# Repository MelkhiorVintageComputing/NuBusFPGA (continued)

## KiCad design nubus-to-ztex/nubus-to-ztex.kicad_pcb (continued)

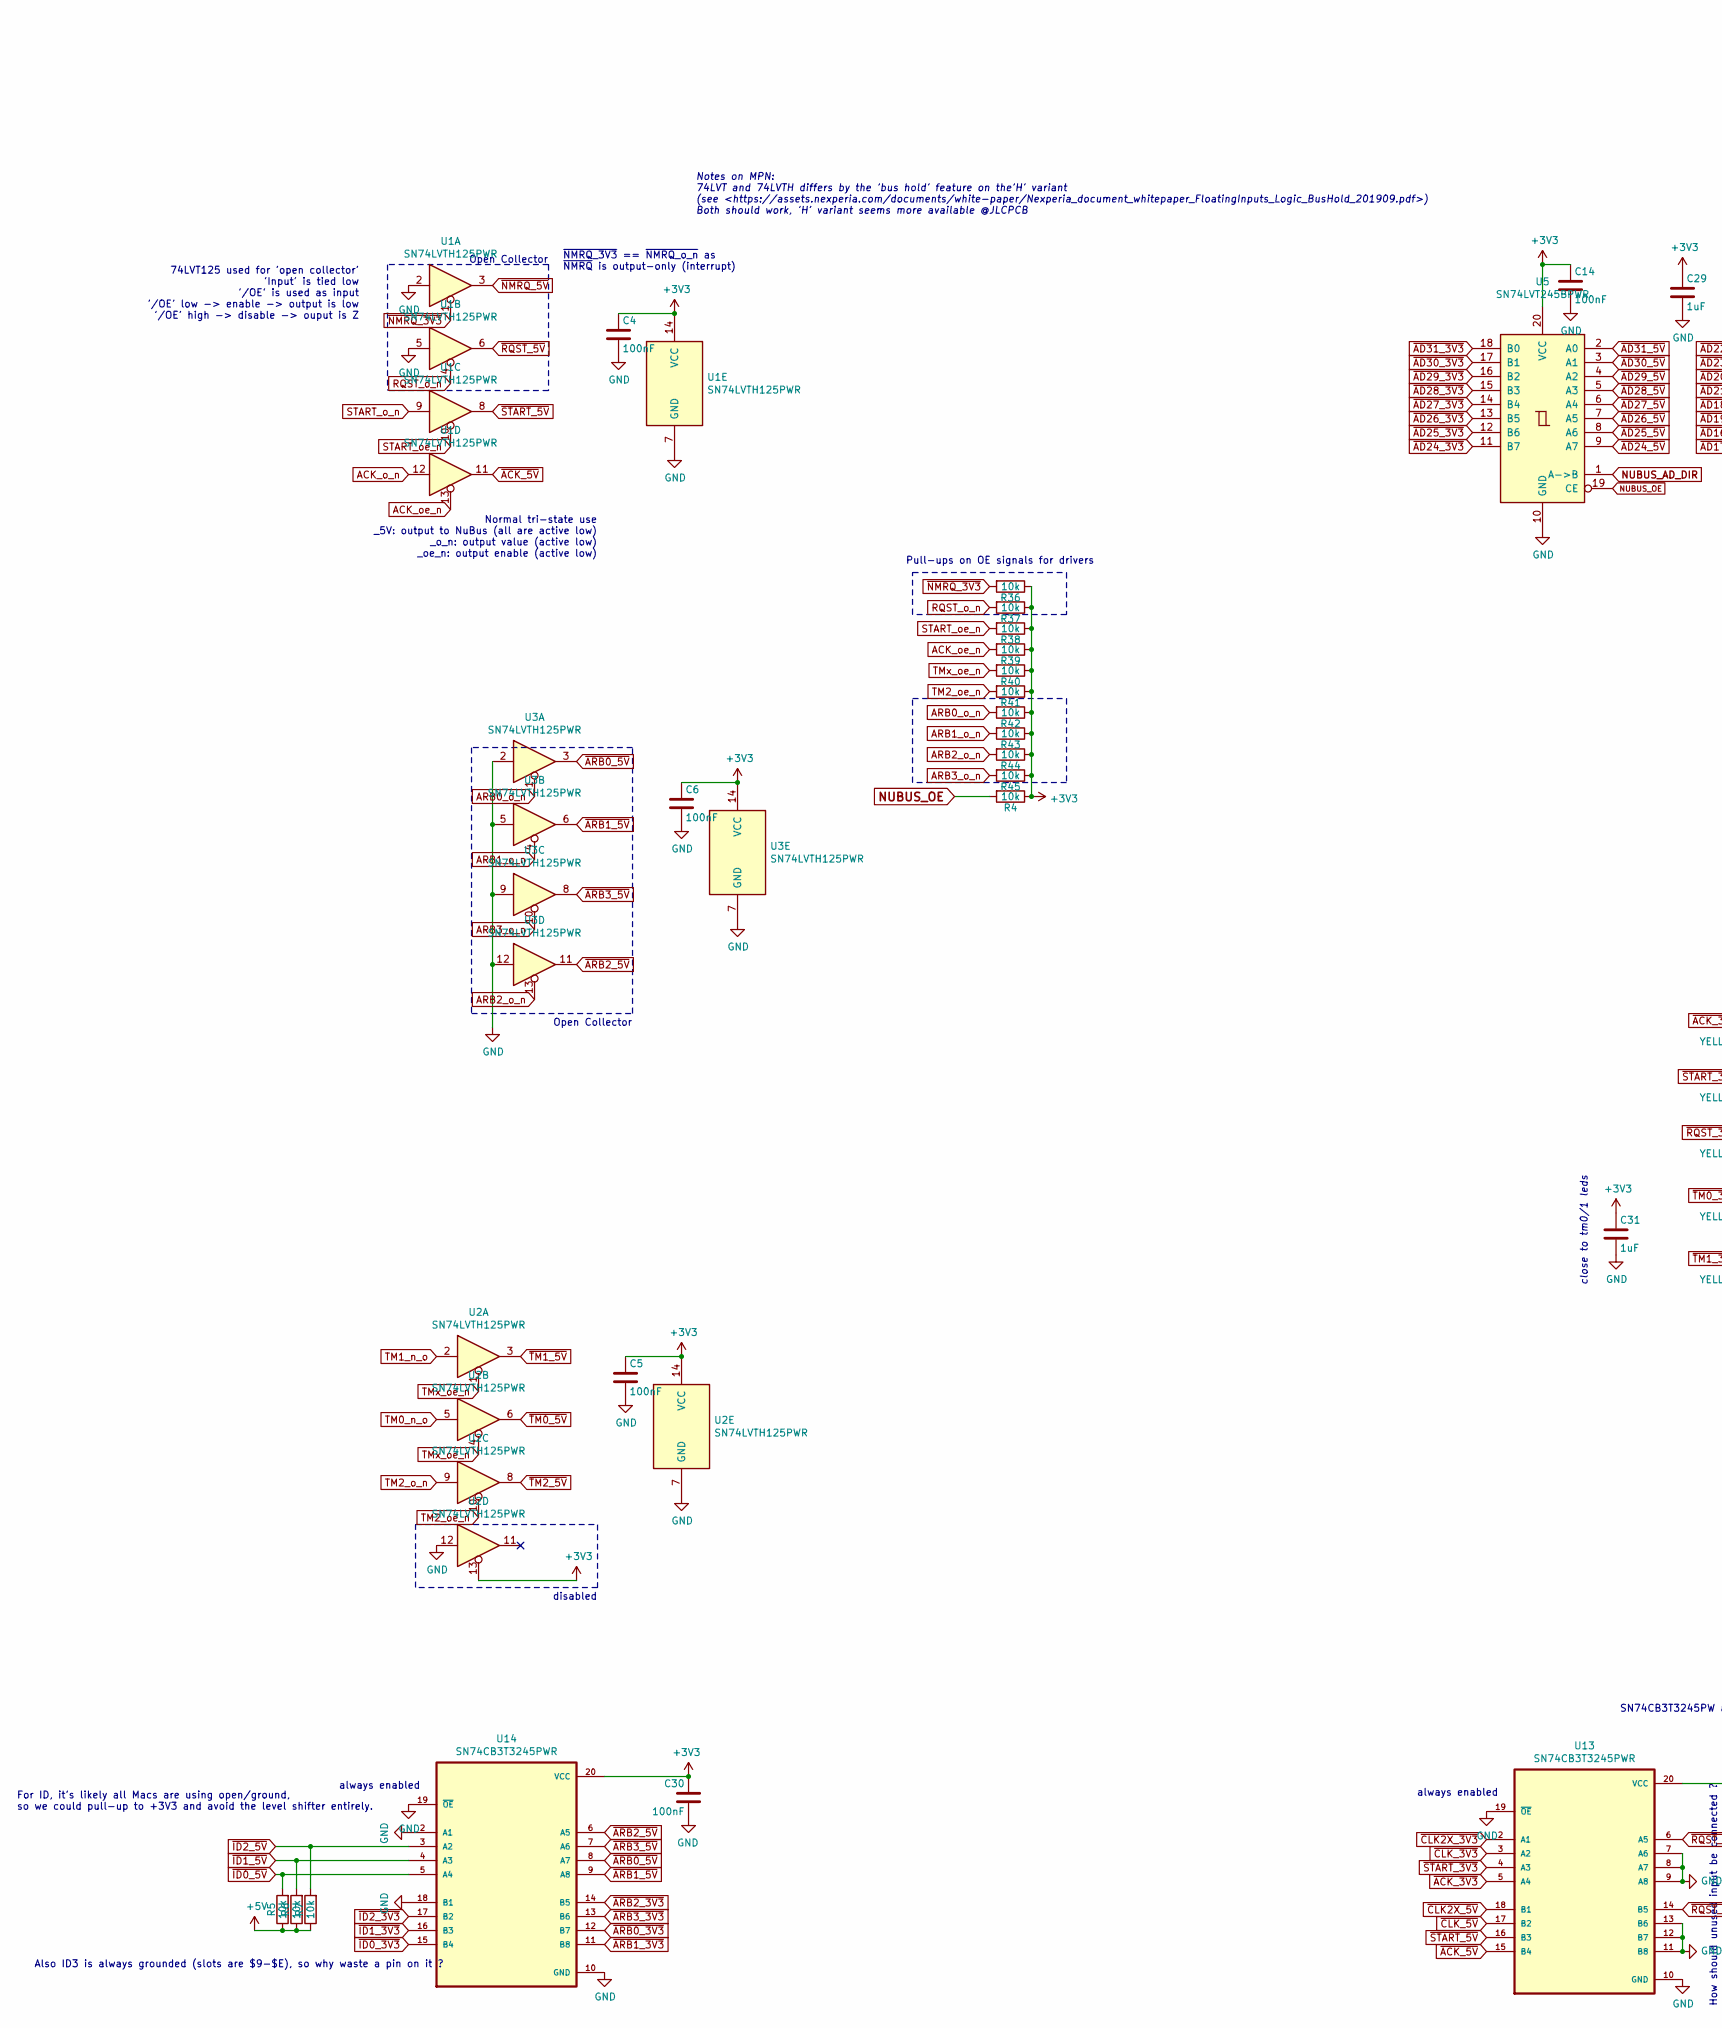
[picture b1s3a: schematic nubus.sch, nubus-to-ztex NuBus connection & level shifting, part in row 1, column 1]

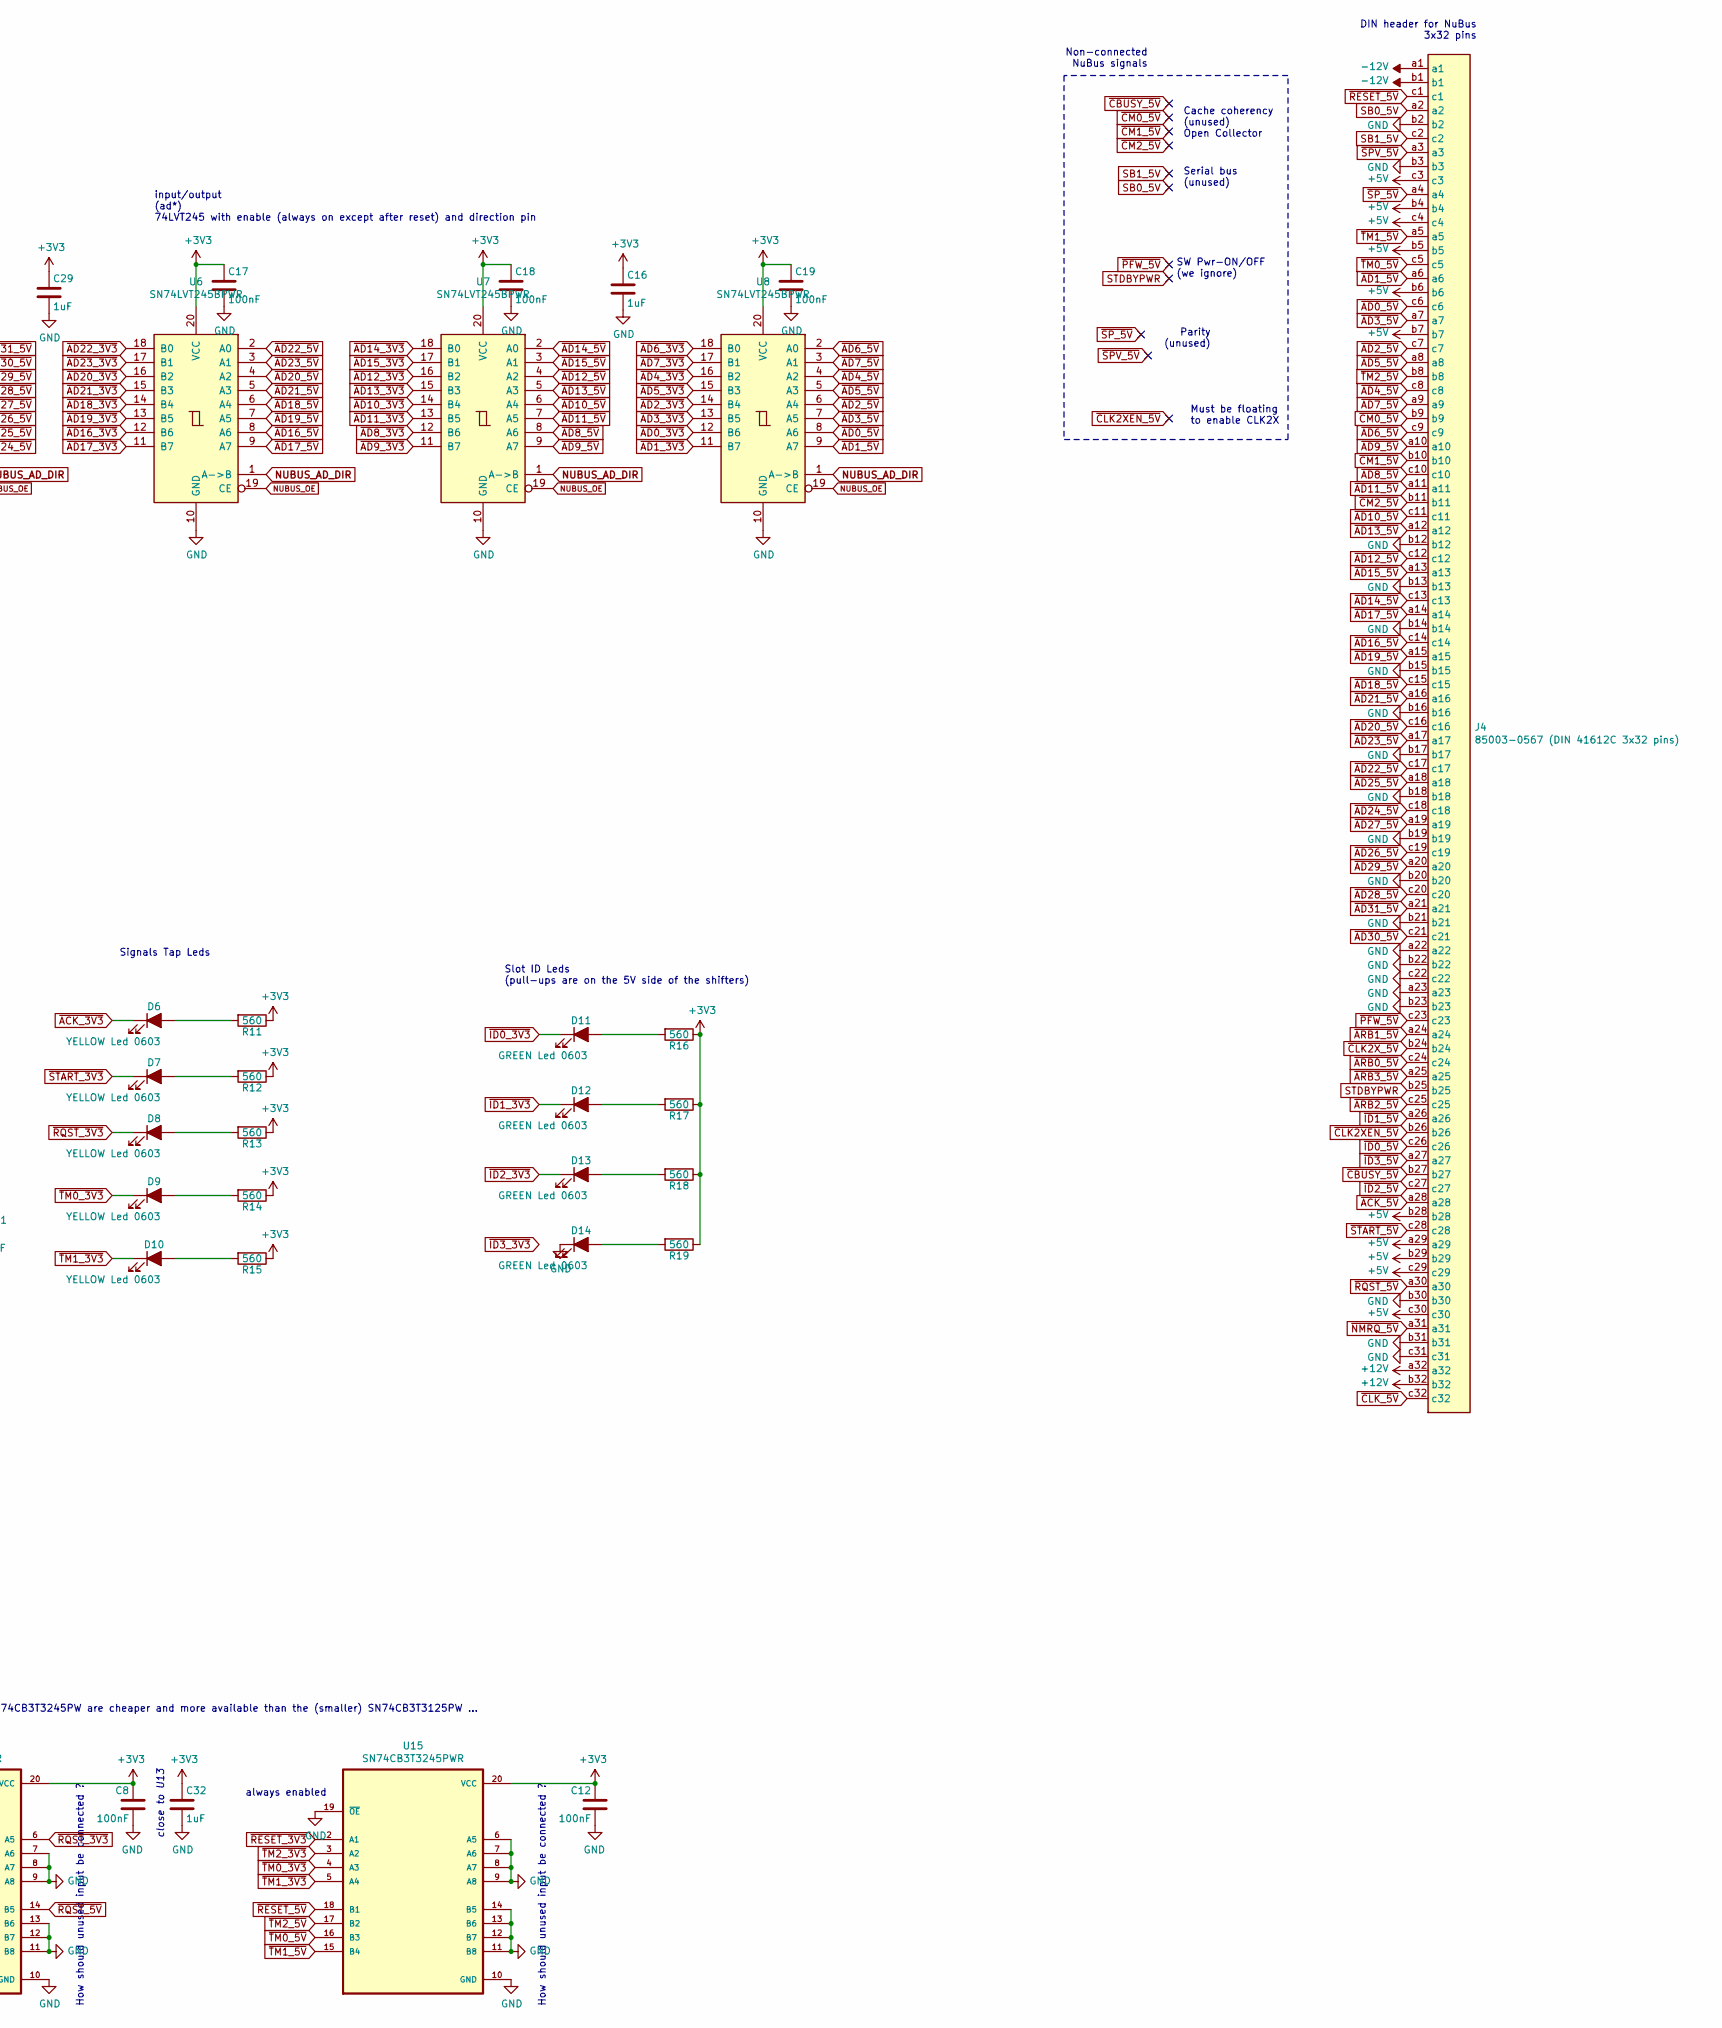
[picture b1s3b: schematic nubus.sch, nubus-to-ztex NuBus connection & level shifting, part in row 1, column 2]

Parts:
C4, C5, C6, C8, C12, C14, C17, C18, C19, C30: 100nF; C_0603_1608Metric; MPN CC0603KRX7R9BB104; Mouser 603-CC603KRX7R8BB104
C16, C29, C31, C32: 1uF; C_0603_1608Metric; MPN CL10A105KB8NNNC
D6, D7, D8, D9, D10: YELLOW Led 0603; LED_0603_1608Metric; MPN 19-213/Y2C-CQ2R2L/3T(CY)
D11, D12, D13, D14: GREEN Led 0603; LED_0603_1608Metric; MPN 19-217/GHC-YR1S2/3T
J4: 85003-0567 (DIN 41612C 3x32 pins); DIN41612_C_3x32_Male_Horizontal_THT; MPN (Molex) 85003-0567
R4, R5, R6, R7, R36, R37, R38, R39, R40, R41, R42, R43, R44, R45: 10k; R_0603_1608Metric; MPN 0603WAF1002T5E
R11, R12, R13, R14, R15, R16, R17, R18, R19: 560; R_0603_1608Metric; MPN 0603WAF5600T5E
U1, U2, U3: SN74LVTH125PWR; TSSOP-14_4.4x5mm_P0.65mm; MPN SN74LVTH125PWR
U5, U6, U7, U8: SN74LVT245BPWR; TSSOP-20_4.4x6.5mm_P0.65mm_ForSeeedStudio; MPN - ALT 74LVT245BPW,118
U13, U14, U15: SN74CB3T3245PWR; TSSOP-20_4.4x6.5mm_P0.65mm_ForSeeedStudio; MPN SN74CB3T3245PWR

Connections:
+3V3: C4.1, C5.1, C6.1, C8.1, C12.1, C14.1, C16.1, C17.1, C18.1, C19.1, C29.1, C30.1, C31.1, C32.1, R4.1, R11.1, R12.1, R13.1, R14.1, R15.1, R16.1, R17.1, R18.1, R19.1, R36.1, R37.1, R38.1, R39.1, R40.1, R41.1, R42.1, R43.1, R44.1, R45.1, U1.14 (VCC), U2.13, U2.14 (VCC), U3.14 (VCC), U5.20 (VCC), U6.20 (VCC), U7.20 (VCC), U8.20 (VCC), U13.20 (VCC), U14.20 (VCC), U15.20 (VCC); also elsewhere on the board
+5V: J4.a29, J4.b4, J4.b5, J4.b6, J4.b7, J4.b28, J4.b29, J4.c3, J4.c4, J4.c29, J4.c30, R5.1, R6.1, R7.1; also elsewhere on the board
+12V: J4.a32, J4.b32
-12V: J4.a1, J4.b1
ACK_o_n: U1.12; also elsewhere on the board
ACK_oe_n: R39.2, U1.13; also elsewhere on the board
ARB0_o_n: R42.2, U3.1; also elsewhere on the board
ARB1_o_n: R43.2, U3.4; also elsewhere on the board
ARB2_o_n: R44.2, U3.13; also elsewhere on the board
ARB3_o_n: R45.2, U3.10; also elsewhere on the board
GND: C4.2, C5.2, C6.2, C8.2, C12.2, C14.2, C16.2, C17.2, C18.2, C19.2, C29.2, C30.2, C31.2, C32.2, D14.1 (K), J4.a22, J4.a23, J4.b2, J4.b3, J4.b12, J4.b13, J4.b14, J4.b15, J4.b16, J4.b17, J4.b18, J4.b19, J4.b20, J4.b21, J4.b22, J4.b23, J4.b30, J4.b31, J4.c22, J4.c31, U1.2, U1.5, U1.7 (GND), U2.7 (GND), U2.12, U3.2, U3.5, U3.7 (GND), U3.9, U3.12, U5.10 (GND), U6.10 (GND), U7.10 (GND), U8.10 (GND), U13.7 (A6), U13.8 (A7), U13.9 (A8), U13.10 (GND), U13.11 (B8), U13.12 (B7), U13.13 (B6), U13.19 (~OE), U14.2 (A1), U14.10 (GND), U14.18 (B1), U14.19 (~OE), U15.6 (A5), U15.7 (A6), U15.8 (A7), U15.9 (A8), U15.10 (GND), U15.11 (B8), U15.12 (B7), U15.13 (B6), U15.14 (B5), U15.19 (~OE); also elsewhere on the board
NUBUS_AD_DIR: U5.1 (A->B), U6.1 (A->B), U7.1 (A->B), U8.1 (A->B); also elsewhere on the board
NUBUS_OE: R4.2, U5.19 (CE), U6.19 (CE), U7.19 (CE), U8.19 (CE); also elsewhere on the board
unnamed: D6.2 (A), R11.2
unnamed: D7.2 (A), R12.2
unnamed: D8.2 (A), R13.2
unnamed: D9.2 (A), R14.2
unnamed: D10.2 (A), R15.2
unnamed: D11.2 (A), R16.2
unnamed: D12.2 (A), R17.2
unnamed: D13.2 (A), R18.2
unnamed: D14.2 (A), R19.2
RQST_o_n: R37.2, U1.4; also elsewhere on the board
SB0_5V: J4.a2
SB1_5V: J4.c2
START_o_n: U1.9; also elsewhere on the board
START_oe_n: R38.2, U1.10; also elsewhere on the board
STDBYPWR: J4.b25
TM0_n_o: U2.5; also elsewhere on the board
TM1_n_o: U2.2; also elsewhere on the board
TM2_o_n: U2.9; also elsewhere on the board
TM2_oe_n: R41.2, U2.10; also elsewhere on the board
TMx_oe_n: R40.2, U2.1, U2.4; also elsewhere on the board
~ACK_3V3: D6.1 (K), U13.5 (A4); also elsewhere on the board
~ACK_5V: J4.a28, U1.11, U13.15 (B4)
~AD0_3V3: U8.12 (B6); also elsewhere on the board
~AD0_5V: J4.c6, U8.8 (A6)
~AD1_3V3: U8.11 (B7); also elsewhere on the board
~AD1_5V: J4.a6, U8.9 (A7)
~AD2_3V3: U8.14 (B4); also elsewhere on the board
~AD2_5V: J4.c7, U8.6 (A4)
~AD3_3V3: U8.13 (B5); also elsewhere on the board
~AD3_5V: J4.a7, U8.7 (A5)
~AD4_3V3: U8.16 (B2); also elsewhere on the board
~AD4_5V: J4.c8, U8.4 (A2)
~AD5_3V3: U8.15 (B3); also elsewhere on the board
~AD5_5V: J4.a8, U8.5 (A3)
~AD6_3V3: U8.18 (B0); also elsewhere on the board
~AD6_5V: J4.c9, U8.2 (A0)
~AD7_3V3: U8.17 (B1); also elsewhere on the board
~AD7_5V: J4.a9, U8.3 (A1)
~AD8_3V3: U7.12 (B6); also elsewhere on the board
~AD8_5V: J4.c10, U7.8 (A6)
~AD9_3V3: U7.11 (B7); also elsewhere on the board
~AD9_5V: J4.a10, U7.9 (A7)
~AD10_3V3: U7.14 (B4); also elsewhere on the board
~AD10_5V: J4.c11, U7.6 (A4)
~AD11_3V3: U7.13 (B5); also elsewhere on the board
~AD11_5V: J4.a11, U7.7 (A5)
~AD12_3V3: U7.16 (B2); also elsewhere on the board
~AD12_5V: J4.c12, U7.4 (A2)
~AD13_3V3: U7.15 (B3); also elsewhere on the board
~AD13_5V: J4.a12, U7.5 (A3)
~AD14_3V3: U7.18 (B0); also elsewhere on the board
~AD14_5V: J4.c13, U7.2 (A0)
~AD15_3V3: U7.17 (B1); also elsewhere on the board
~AD15_5V: J4.a13, U7.3 (A1)
~AD16_3V3: U6.12 (B6); also elsewhere on the board
~AD16_5V: J4.c14, U6.8 (A6)
~AD17_3V3: U6.11 (B7); also elsewhere on the board
~AD17_5V: J4.a14, U6.9 (A7)
~AD18_3V3: U6.14 (B4); also elsewhere on the board
~AD18_5V: J4.c15, U6.6 (A4)
~AD19_3V3: U6.13 (B5); also elsewhere on the board
~AD19_5V: J4.a15, U6.7 (A5)
~AD20_3V3: U6.16 (B2); also elsewhere on the board
~AD20_5V: J4.c16, U6.4 (A2)
~AD21_3V3: U6.15 (B3); also elsewhere on the board
~AD21_5V: J4.a16, U6.5 (A3)
~AD22_3V3: U6.18 (B0); also elsewhere on the board
~AD22_5V: J4.c17, U6.2 (A0)
~AD23_3V3: U6.17 (B1); also elsewhere on the board
~AD23_5V: J4.a17, U6.3 (A1)
~AD24_3V3: U5.11 (B7); also elsewhere on the board
~AD24_5V: J4.c18, U5.9 (A7)
~AD25_3V3: U5.12 (B6); also elsewhere on the board
~AD25_5V: J4.a18, U5.8 (A6)
~AD26_3V3: U5.13 (B5); also elsewhere on the board
~AD26_5V: J4.c19, U5.7 (A5)
~AD27_3V3: U5.14 (B4); also elsewhere on the board
~AD27_5V: J4.a19, U5.6 (A4)
~AD28_3V3: U5.15 (B3); also elsewhere on the board
~AD28_5V: J4.c20, U5.5 (A3)
~AD29_3V3: U5.16 (B2); also elsewhere on the board
~AD29_5V: J4.a20, U5.4 (A2)
~AD30_3V3: U5.17 (B1); also elsewhere on the board
~AD30_5V: J4.c21, U5.3 (A1)
~AD31_3V3: U5.18 (B0); also elsewhere on the board
~AD31_5V: J4.a21, U5.2 (A0)
~ARB0_3V3: U14.12 (B7); also elsewhere on the board
~ARB0_5V: J4.c24, U3.3, U14.8 (A7)
~ARB1_3V3: U14.11 (B8); also elsewhere on the board
~ARB1_5V: J4.a24, U3.6, U14.9 (A8)
~ARB2_3V3: U14.14 (B5); also elsewhere on the board
~ARB2_5V: J4.c25, U3.11, U14.6 (A5)
~ARB3_3V3: U14.13 (B6); also elsewhere on the board
~ARB3_5V: J4.a25, U3.8, U14.7 (A6)
~CBUSY_5V: J4.b27
~CLK2XEN_5V: J4.b26
~CLK2X_3V3: U13.2 (A1); also elsewhere on the board
~CLK2X_5V: J4.b24, U13.18 (B1)
~CLK_3V3: U13.3 (A2); also elsewhere on the board
~CLK_5V: J4.c32, U13.17 (B2)
~CM0_5V: J4.b9
~CM1_5V: J4.b10
~CM2_5V: J4.b11
~ID0_3V3: D11.1 (K), U14.15 (B4); also elsewhere on the board
~ID0_5V: J4.c26, R5.2, U14.5 (A4)
~ID1_3V3: D12.1 (K), U14.16 (B3); also elsewhere on the board
~ID1_5V: J4.a26, R6.2, U14.4 (A3)
~ID2_3V3: D13.1 (K), U14.17 (B2); also elsewhere on the board
~ID2_5V: J4.c27, R7.2, U14.3 (A2)
~ID3_5V: J4.a27
~NMRQ_3V3: R36.2, U1.1; also elsewhere on the board
~NMRQ_5V: J4.a31, U1.3
~PFW_5V: J4.c23
~RESET_3V3: U15.2 (A1); also elsewhere on the board
~RESET_5V: J4.c1, U15.18 (B1)
~RQST_3V3: D8.1 (K), U13.6 (A5); also elsewhere on the board
~RQST_5V: J4.a30, U1.6, U13.14 (B5)
~SPV_5V: J4.a3
~SP_5V: J4.a4
~START_3V3: D7.1 (K), U13.4 (A3); also elsewhere on the board
~START_5V: J4.c28, U1.8, U13.16 (B3)
~TM0_3V3: D9.1 (K), U15.4 (A3); also elsewhere on the board
~TM0_5V: J4.c5, U2.6, U15.16 (B3)
~TM1_3V3: D10.1 (K), U15.5 (A4); also elsewhere on the board
~TM1_5V: J4.a5, U2.3, U15.15 (B4)
~TM2_3V3: U15.3 (A2); also elsewhere on the board
~TM2_5V: J4.b8, U2.8, U15.17 (B2)

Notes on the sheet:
Cache coherency (unused) Open Collector
Serial bus (unused)
Must be floating to enable CLK2X
SW Pwr-ON/OFF (we ignore)
input/output (ad*) 74LVT245 with enable (always on except after reset) and direction pin
Slot ID Leds (pull-ups are on the 5V side of the shifters)
74LVT125 used for 'open collector' 'Input' is tied low '/OE' is used as input '/OE' low -> enable -> output is low '/OE' high -> disable -> ouput is Z
Parity (unused)
Open Collector
Normal tri-state use _5V: output to NuBus (all are active low) _o_n: output value (active low) _oe_n: output enable (active low)
DIN header for NuBus 3x32 pins
Non-connected NuBus signals
disabled
Pull-ups on OE signals for drivers
always enabled
For ID, it's likely all Macs are using open/ground, so we could pull-up to +3V3 and avoid the level shifter entirely.
Signals Tap Leds
How should unused input be connected ?
SN74CB3T3245PW are cheaper and more available than the (smaller) SN74CB3T3125PW ...
~NMRQ_3V3~ == ~NMRQ_o_n~ as ~NMRQ~ is output-only (interrupt)
Also ID3 is always grounded (slots are $9-$E), so why waste a pin on it ?
Notes on MPN: 74LVT and 74LVTH differs by the 'bus hold' feature on the'H' variant (see <https://assets.nexperia.com/documents/white-paper/Nexperia_document_whitepaper_FloatingInputs_Logic_BusHold_201909.pdf>) Both should work, 'H' variant seems more available @JLCPCB
close to tm0/1 leds
close to U13

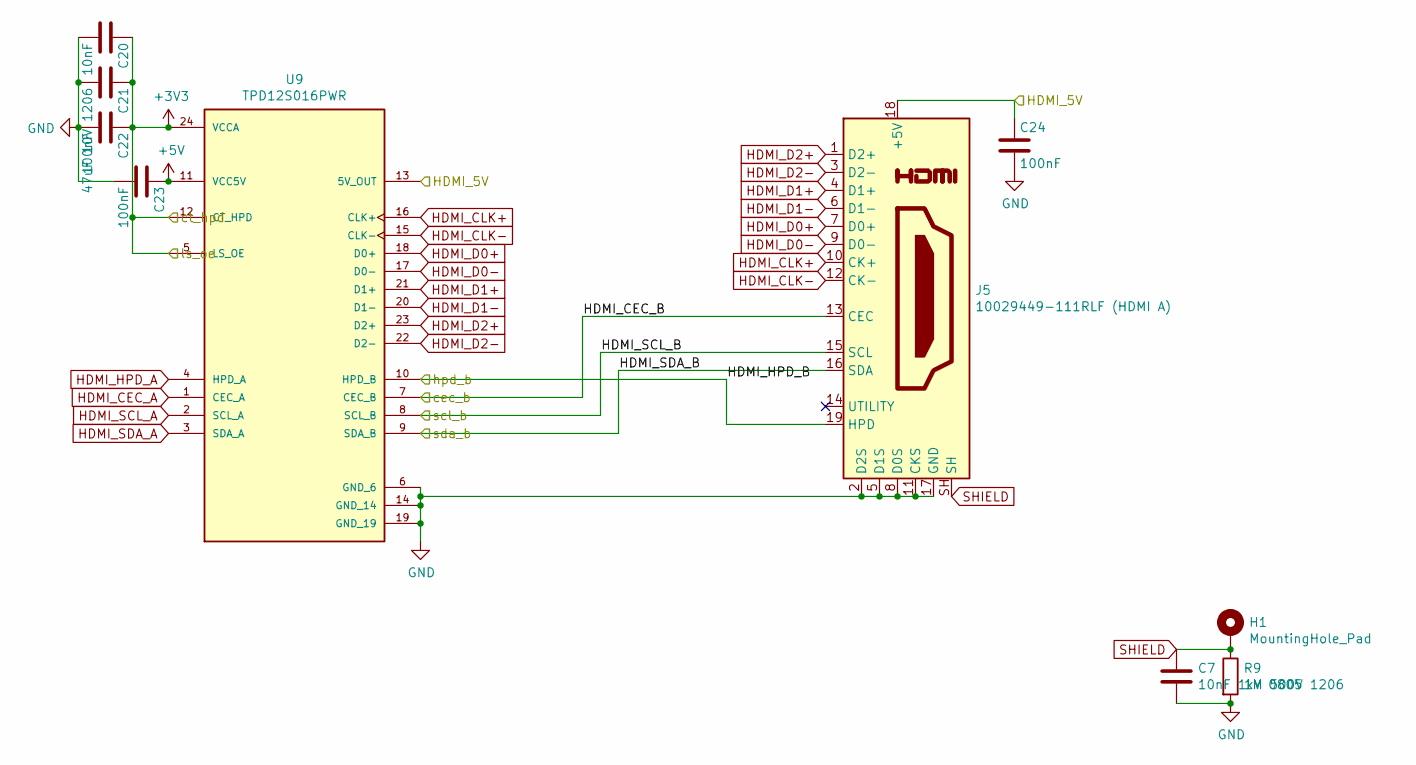
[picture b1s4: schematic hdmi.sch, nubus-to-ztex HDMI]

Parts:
C7: 10nF 1kV 0805; C_0805_2012Metric; MPN-ALT C0805V103KCRACTU
C20: 10nF; C_0603_1608Metric; MPN 0603B103K500NT; Mouser 603-CC603KRX7R8BB103
C21: 47uF 10V 1206; C_1206_3216Metric; MPN-ALT3 GRM21BR61A476ME15L # 10V
C22, C23, C24: 100nF; C_0603_1608Metric; MPN CC0603KRX7R9BB104; Mouser 603-CC603KRX7R8BB104
H1: MountingHole_Pad; MountingHole_2.2mm_M2_Pad
J5: 10029449-111RLF (HDMI A); HDMI_A_Amphenol_10029449-111; MPN 10029449-111RLF
R9: 1M 500V 1206; R_1206_3216Metric; MPN HR1206J1M00P05Z
U9: TPD12S016PWR; SOP65P640X120-24N; PARTREV F

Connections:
+3V3: C20.1, C21.1, C22.1, U9.5 (LS_OE), U9.12 (CT_HPD), U9.24 (VCCA); also elsewhere on the board
+5V: C23.1, U9.11 (VCC5V); also elsewhere on the board
/hdmi/HDMI_5V: C24.1, J5.18 (+5V), U9.13 (5V_OUT)
/hdmi/cec_b: J5.13 (CEC), U9.7 (CEC_B)
/hdmi/hpd_b: J5.19 (HPD), U9.10 (HPD_B)
/hdmi/scl_b: J5.15 (SCL), U9.8 (SCL_B)
/hdmi/sda_b: J5.16 (SDA), U9.9 (SDA_B)
GND: C7.2, C20.2, C21.2, C22.2, C23.2, C24.2, J5.2 (D2S), J5.5 (D1S), J5.8 (D0S), J5.11 (CKS), J5.17 (GND), R9.2, U9.6 (GND_6), U9.14 (GND_14), U9.19 (GND_19); also elsewhere on the board
HDMI_CEC_A: U9.1 (CEC_A); also elsewhere on the board
HDMI_CLK+: J5.10 (CK+), U9.16 (CLK+); also elsewhere on the board
HDMI_CLK-: J5.12 (CK-), U9.15 (CLK-); also elsewhere on the board
HDMI_D0+: J5.7 (D0+), U9.18 (D0+); also elsewhere on the board
HDMI_D0-: J5.9 (D0-), U9.17 (D0-); also elsewhere on the board
HDMI_D1+: J5.4 (D1+), U9.21 (D1+); also elsewhere on the board
HDMI_D1-: J5.6 (D1-), U9.20 (D1-); also elsewhere on the board
HDMI_D2+: J5.1 (D2+), U9.23 (D2+); also elsewhere on the board
HDMI_D2-: J5.3 (D2-), U9.22 (D2-); also elsewhere on the board
HDMI_HPD_A: U9.4 (HPD_A); also elsewhere on the board
HDMI_SCL_A: U9.2 (SCL_A); also elsewhere on the board
HDMI_SDA_A: U9.3 (SDA_A); also elsewhere on the board
SHIELD: C7.1, H1.1, J5.SH, R9.1; also elsewhere on the board

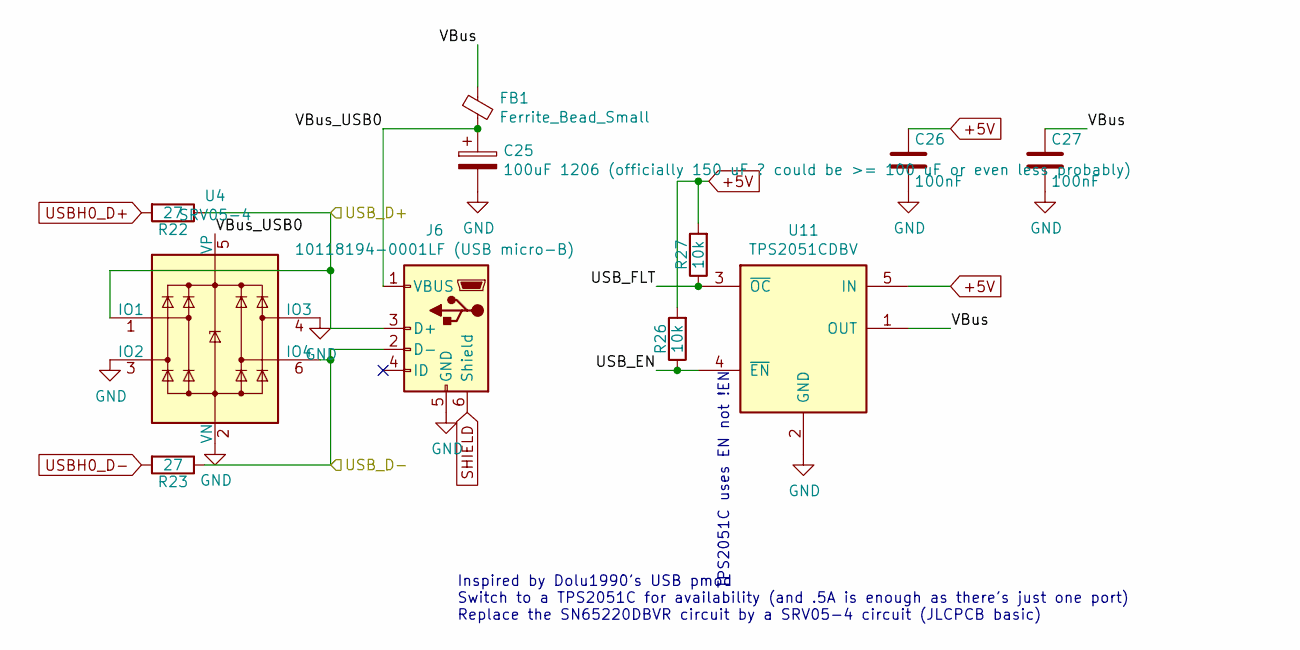
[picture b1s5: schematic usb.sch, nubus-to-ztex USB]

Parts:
C25: 100uF 1206 (officially 150 uF ? could be >= 100 u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; C_1206_3216Metric; MPN-ALT GRM31CR60J157ME11L
C26, C27: 100nF; C_0603_1608Metric; MPN CC0603KRX7R9BB104; Digikey ?
FB1: Ferrite_Bead_Small; L_0805_2012Metric; MPN-ALT 742792022
J6: 10118194-0001LF (USB micro-B); USB_Micro-B_Amphenol_10118194_Horizontal; MPN 10118194-0001LF
R22, R23: 27; R_0603_1608Metric; MPN 0603WAF270JT5E
R26, R27: 10k; R_0603_1608Metric; MPN 0603WAF1002T5E
U4: SRV05-4; SOT-23-6; MPN SRV05-4-P-T7
U11: TPS2051CDBV; SOT-23-5; MPN TPS2051CDBVR; Mouser No 595-TPS2051CDBVR

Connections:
+5V: C26.1, R26.2, R27.2, U11.5 (IN); also elsewhere on the board
/usb/USB_D+: J6.3 (D+), R22.1, U4.1 (IO1)
/usb/USB_D-: J6.2 (D-), R23.1, U4.6 (IO4)
/usb/USB_EN: R26.1, U11.4 (~EN)
/usb/USB_FLT: R27.1, U11.3 (~OC)
/usb/VBus: C27.1, FB1.1, U11.1 (OUT)
/usb/VBus_USB0: C25.1, FB1.2, J6.1 (VBUS), U4.5 (VP)
GND: C25.2, C26.2, C27.2, J6.5 (GND), U4.2 (VN), U4.3 (IO2), U4.4 (IO3), U11.2 (GND); also elsewhere on the board
SHIELD: J6.6 (Shield); also elsewhere on the board
USBH0_D+: R22.2; also elsewhere on the board
USBH0_D-: R23.2; also elsewhere on the board

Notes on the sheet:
Inspired by Dolu1990's USB pmod Switch to a TPS2051C for availability (and .5A is enough as there's just one port) Replace the SN65220DBVR circuit by a SRV05-4 circuit (JLCPCB basic)
TPS2051C uses EN not !EN

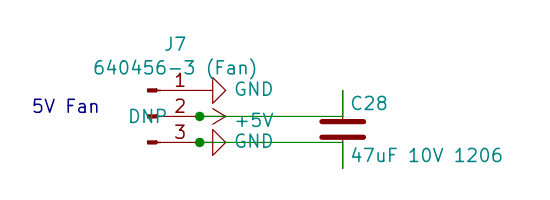
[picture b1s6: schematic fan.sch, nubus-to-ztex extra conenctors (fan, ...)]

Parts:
C28: 47uF 10V 1206; C_1206_3216Metric; MPN-ALT C2012X5R1A476MTJ00E
J7: 640456-3 (Fan); Molex_KK-254_AE-6410-03A_1x03_P2.54mm_Vertical; MPN-ALT 22-27-2031

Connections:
+5V: C28.1, J7.2; also elsewhere on the board
GND: C28.2, J7.1, J7.3; also elsewhere on the board

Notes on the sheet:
5V Fan

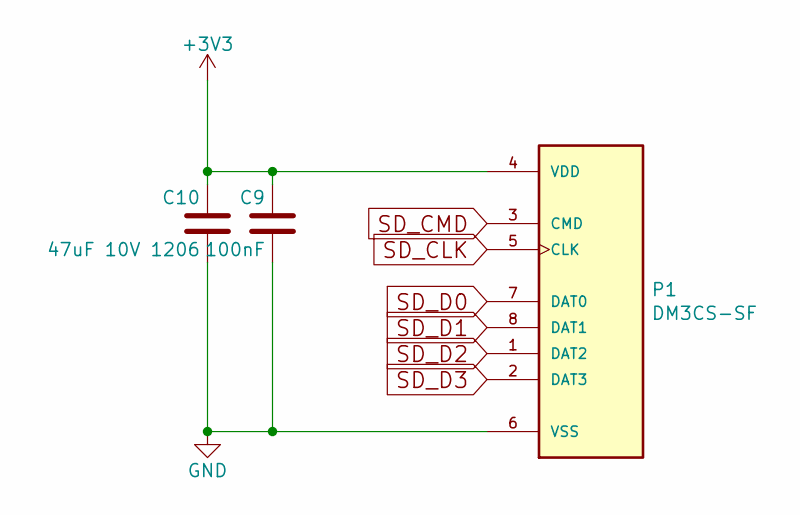
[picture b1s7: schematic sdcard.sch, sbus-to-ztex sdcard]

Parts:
C2: 100nF; C_0603_1608Metric; MPN CC0603KRX7R9BB104; Mouser 603-CC603KRX7R8BB104
C10: 47uF 10V 1206; C_1206_3216Metric; MPN-ALT GRM21BR60J476ME15L
P1: DM3CS-SF; HRS_DM3CS-SF; MPN DM3CS-SF

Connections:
+3V3: C2.1, C10.1, P1.4 (VDD); also elsewhere on the board
GND: C2.2, C10.2, P1.6 (VSS); also elsewhere on the board
SD_CLK: P1.5 (CLK); also elsewhere on the board
SD_CMD: P1.3 (CMD); also elsewhere on the board
SD_D0: P1.7 (DAT0); also elsewhere on the board
SD_D1: P1.8 (DAT1); also elsewhere on the board
SD_D2: P1.1 (DAT2); also elsewhere on the board
SD_D3: P1.2 (DAT3); also elsewhere on the board

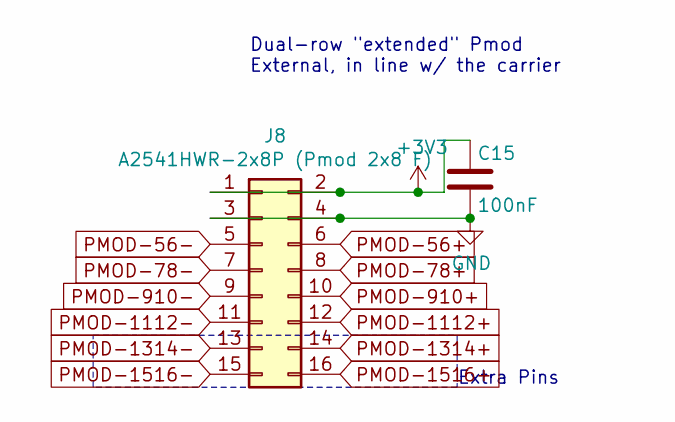
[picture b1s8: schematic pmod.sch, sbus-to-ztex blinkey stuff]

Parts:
C15: 100nF; C_0603_1608Metric; MPN CC0603KRX7R9BB104; Mouser 603-CC603KRX7R8BB104
J8: A2541HWR-2x8P (Pmod 2x8 F); PinSocket_2x08_P2.54mm_Horizontal_ForSeeedStudio; MPN A2541HWR-2x8P

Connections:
+3V3: C15.1, J8.1, J8.2; also elsewhere on the board
GND: C15.2, J8.3, J8.4; also elsewhere on the board
PMOD-56+: J8.6; also elsewhere on the board
PMOD-56-: J8.5; also elsewhere on the board
PMOD-78+: J8.8; also elsewhere on the board
PMOD-78-: J8.7; also elsewhere on the board
PMOD-910+: J8.10; also elsewhere on the board
PMOD-910-: J8.9; also elsewhere on the board
PMOD-1112+: J8.12; also elsewhere on the board
PMOD-1112-: J8.11; also elsewhere on the board
PMOD-1314+: J8.14; also elsewhere on the board
PMOD-1314-: J8.13; also elsewhere on the board
PMOD-1516+: J8.16; also elsewhere on the board
PMOD-1516-: J8.15; also elsewhere on the board

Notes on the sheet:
Dual-row "extended" Pmod External, in line w/ the carrier
Extra Pins

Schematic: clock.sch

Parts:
C11: 100nF; C_0603_1608Metric; MPN CC0603KRX7R9BB104; Mouser 603-CC603KRX7R8BB104
C13: 10nF; C_0603_1608Metric; MPN 0603B103K500NT; Mouser 603-CC603KRX7R8BB103
R8: 27; R_0603_1608Metric; MPN 0603WAF270JT5E
X1: ASE-xxxMHz; Oscillator_SMD_Abracon_ASE-4Pin_3.2x2.5mm; MPN SX3M54.000M20F30TNN

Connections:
+3V3: C11.1, C13.1, X1.4 (Vdd); also elsewhere on the board
CLK_54_000: R8.1; also elsewhere on the board
GND: C11.2, C13.2, X1.2 (GND); also elsewhere on the board
unnamed: R8.2, X1.3 (OUT)

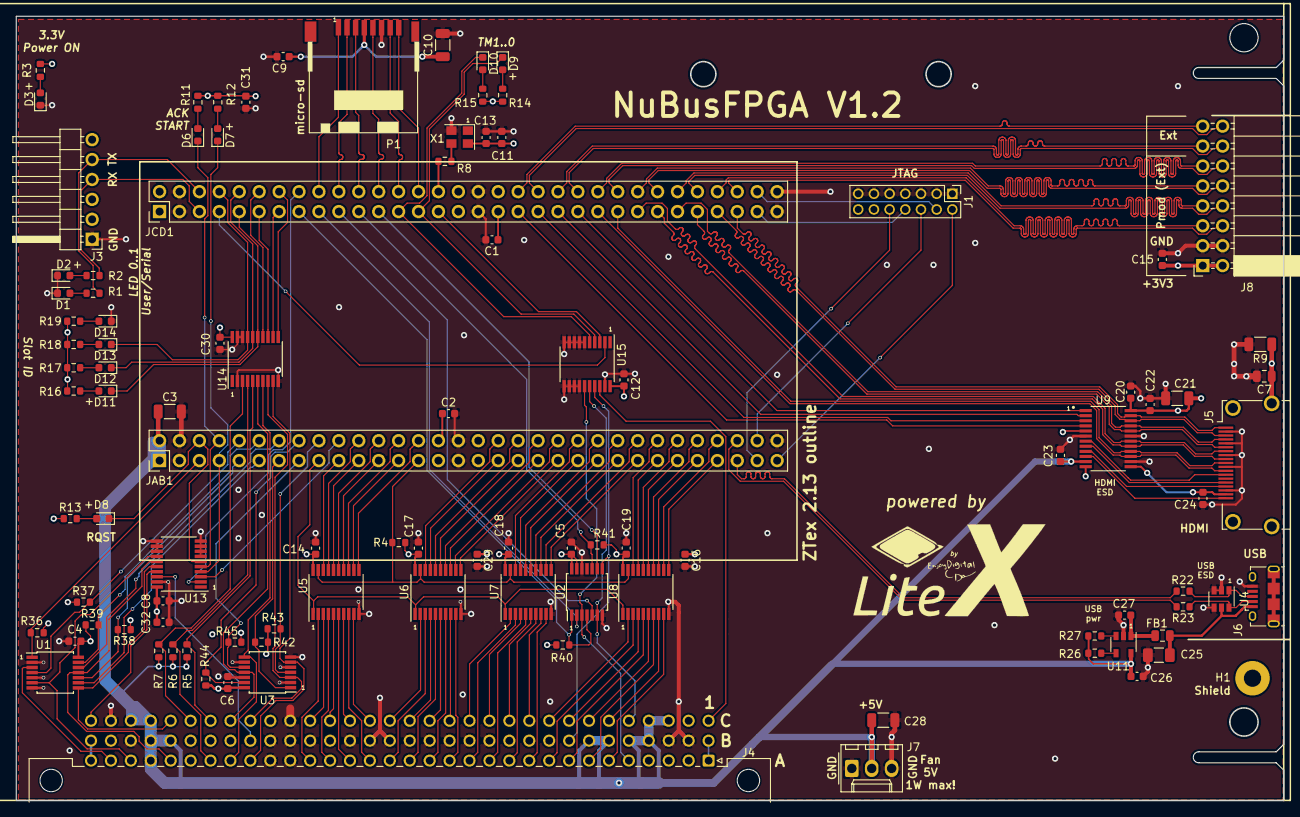
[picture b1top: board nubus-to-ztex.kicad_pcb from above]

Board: 4 copper layers, 161.6 x 100.0 mm, 103 parts (0 on the bottom side), 184 nets.

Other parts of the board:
C9: 100nF; C_0603_1608Metric

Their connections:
+3V3: C9.1; also elsewhere on the board
GND: C9.2; also elsewhere on the board

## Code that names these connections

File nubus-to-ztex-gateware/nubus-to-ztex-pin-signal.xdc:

# !!! Constraint files are application specific !!!
# !!!          This is a template only          !!!

# on-board signals

# CLKOUT/FXCLK 
create_clock -name fxclk_in -period 20.833 [get_ports fxclk_in]
set_property PACKAGE_PIN P15 [get_ports fxclk_in]
set_property IOSTANDARD LVCMOS33 [get_ports fxclk_in]

# IFCLK 
#create_clock -name ifclk_in -period 20.833 [get_ports ifclk_in]
#set_property PACKAGE_PIN P17 [get_ports ifclk_in]
#set_property IOSTANDARD LVCMOS33 [get_ports ifclk_in]

set_property CONFIG_VOLTAGE 3.3 [current_design]
set_property CFGBVS VCCO [current_design]
set_property BITSTREAM.CONFIG.CONFIGRATE 66 [current_design]  
set_property BITSTREAM.CONFIG.SPI_32BIT_ADDR No [current_design]
set_property BITSTREAM.CONFIG.SPI_BUSWIDTH 2 [current_design]
set_property BITSTREAM.GENERAL.COMPRESS true [current_design]


# set_property PACKAGE_PIN  [get_ports {}]
# set_property IOSTANDARD LVTTL [get_ports {}]

#### AB
# AB TOP LEFT (12)
set_property PACKAGE_PIN K16 [get_ports {nmrq_n}]
set_property PACKAGE_PIN K15 [get_ports {start_n}]
set_property PACKAGE_PIN J15 [get_ports {start_oe_n}]
set_property PACKAGE_PIN H15 [get_ports {start_o_n}]
set_property PACKAGE_PIN J14 [get_ports {arb_o_n[0]}]
set_property PACKAGE_PIN H17 [get_ports {arb_o_n[3]}]
set_property PACKAGE_PIN G17 [get_ports {nubus_ad_dir}]
set_property PACKAGE_PIN G18 [get_ports {ad_n[31]}]
set_property PACKAGE_PIN F18 [get_ports {ad_n[29]}]
set_property PACKAGE_PIN E18 [get_ports {ad_n[27]}]
set_property PACKAGE_PIN D18 [get_ports {ad_n[25]}]
set_property PACKAGE_PIN G13 [get_ports {nubus_oe}]

# AB BOTTOM LEFT (13)
set_property PACKAGE_PIN F13 [get_ports {ad_n[23]}]
set_property PACKAGE_PIN E16 [get_ports {ad_n[21]}]
set_property PACKAGE_PIN C17 [get_ports {ad_n[19]}]
set_property PACKAGE_PIN A18 [get_ports {ad_n[17]}]
set_property PACKAGE_PIN C15 [get_ports {ad_n[15]}]
set_property PACKAGE_PIN B17 [get_ports {ad_n[13]}]
set_property PACKAGE_PIN C14 [get_ports {ad_n[11]}]
set_property PACKAGE_PIN D13 [get_ports {ad_n[9]}]
set_property PACKAGE_PIN A16 [get_ports {ad_n[7]}]
set_property PACKAGE_PIN B14 [get_ports {ad_n[5]}]
set_property PACKAGE_PIN B12 [get_ports {ad_n[3]}]
set_property PACKAGE_PIN A14 [get_ports {ad_n[1]}]
set_property PACKAGE_PIN B11 [get_ports {usbh0_p}]

# AB TOP RIGHT (12)
set_property PACKAGE_PIN J18 [get_ports {rqst_n}]
set_property PACKAGE_PIN J17 [get_ports {ack_n}]
set_property PACKAGE_PIN K13 [get_ports {rsqt_o_n}]
set_property PACKAGE_PIN J13 [get_ports {ack_oe_n}]
set_property PACKAGE_PIN H14 [get_ports {ack_o_n}]
set_property PACKAGE_PIN G14 [get_ports {arb_o_n[2]}]
set_property PACKAGE_PIN G16 [get_ports {arb_o_n[1]}]
set_property PACKAGE_PIN H16 [get_ports {clk_n}]
set_property PACKAGE_PIN F16 [get_ports {ad_n[30]}]
set_property PACKAGE_PIN F15 [get_ports {ad_n[28]}]
set_property PACKAGE_PIN E17 [get_ports {ad_n[26]}]
set_property PACKAGE_PIN D17 [get_ports {ad_n[24]}]

# AB BOTTOM RIGHT (13)
set_property PACKAGE_PIN F14 [get_ports {ad_n[22]}]
set_property PACKAGE_PIN E15 [get_ports {ad_n[20]}]
set_property PACKAGE_PIN C16 [get_ports {ad_n[18]}]
set_property PACKAGE_PIN B18 [get_ports {ad_n[16]}]
set_property PACKAGE_PIN D15 [get_ports {ad_n[14]}]
set_property PACKAGE_PIN B16 [get_ports {ad_n[12]}]
set_property PACKAGE_PIN D14 [get_ports {ad_n[10]}]
set_property PACKAGE_PIN D12 [get_ports {ad_n[8]}]
set_property PACKAGE_PIN A15 [get_ports {ad_n[6]}]
set_property PACKAGE_PIN B13 [get_ports {ad_n[4]}]
set_property PACKAGE_PIN C12 [get_ports {ad_n[2]}]
set_property PACKAGE_PIN A13 [get_ports {ad_n[0]}]
set_property PACKAGE_PIN A11 [get_ports {usbh0_n}]

#### CD
# CD TOP LEFT (13)
set_property PACKAGE_PIN U9 [get_ports {RX}]
set_property PACKAGE_PIN U8 [get_ports {id_n[3]}]
set_property PACKAGE_PIN U7 [get_ports {id_n[0]}]
set_property PACKAGE_PIN U6 [get_ports {arb_n[3]}]
set_property PACKAGE_PIN T8 [get_ports {arb_n[0]}]
set_property PACKAGE_PIN R8 [get_ports {tmx_oe_n}]
set_property PACKAGE_PIN R7 [get_ports {tm_o_n[1]}]
set_property PACKAGE_PIN T6 [get_ports {tm_o_n[0]}]
set_property PACKAGE_PIN R6 [get_ports {tm2_oe_n}]
set_property PACKAGE_PIN R5 [get_ports {tm_o_n[2]}]
set_property PACKAGE_PIN V2 [get_ports {tm_n[1]}]
set_property PACKAGE_PIN U2 [get_ports {tm_n[0]}]
set_property PACKAGE_PIN K6 [get_ports {tm_n[2]}]

# CD BOTTOM LEFT (12)
set_property PACKAGE_PIN N6 [get_ports {hdmi_hpd_a}]
set_property PACKAGE_PIN M6 [get_ports {hdmi_sda_a}]
set_property PACKAGE_PIN L6 [get_ports {hdmi_scl_a}]
set_property PACKAGE_PIN L5 [get_ports {hdmi_cec_a}]
set_property PACKAGE_PIN N4 [get_ports {hdmi_clk_n}]
set_property PACKAGE_PIN M4 [get_ports {hdmi_clk_p}]
set_property PACKAGE_PIN M3 [get_ports {hdmi_d0_p}]
set_property PACKAGE_PIN M2 [get_ports {hdmi_d0_n}]
set_property PACKAGE_PIN K5 [get_ports {hdmi_d1_p}]
set_property PACKAGE_PIN L4 [get_ports {hdmi_d1_n}]
set_property PACKAGE_PIN L3 [get_ports {hdmi_d2_n}]
set_property PACKAGE_PIN K3 [get_ports {hdmi_d2_p}]

# CD TOP RIGHT (13)
set_property PACKAGE_PIN V9 [get_ports {TX}]
set_property PACKAGE_PIN V7 [get_ports {id_n[2]}]
set_property PACKAGE_PIN V6 [get_ports {id_n[1]}]
set_property PACKAGE_PIN V5 [get_ports {arb_n[2]}]
set_property PACKAGE_PIN V4 [get_ports {arb_n[1]}]
set_property PACKAGE_PIN T5 [get_ports {clk2x_n}]
set_property PACKAGE_PIN T4 [get_ports {SD_D2}]
set_property PACKAGE_PIN U4 [get_ports {SD_D3}]
set_property PACKAGE_PIN U3 [get_ports {SD_CMD}]
set_property PACKAGE_PIN V1 [get_ports {SD_CLK}]
set_property PACKAGE_PIN U1 [get_ports {SD_D0}]
set_property PACKAGE_PIN T3 [get_ports {SD_D1}]
set_property PACKAGE_PIN R3 [get_ports {reset_n}]

# CD BOTTOM RIGHT (12)
set_property PACKAGE_PIN P5 [get_ports {PMOD15}]
set_property PACKAGE_PIN N5 [get_ports {PMOD16}]
set_property PACKAGE_PIN P4 [get_ports {PMOD13}]
set_property PACKAGE_PIN P3 [get_ports {PMOD14}]
set_property PACKAGE_PIN T1 [get_ports {PMOD11}]
set_property PACKAGE_PIN R1 [get_ports {PMOD12}]
set_property PACKAGE_PIN R2 [get_ports {PMOD9}]
set_property PACKAGE_PIN P2 [get_ports {PMOD10}]
set_property PACKAGE_PIN N2 [get_ports {PMOD7}]
set_property PACKAGE_PIN N1 [get_ports {PMOD8}]
set_property PACKAGE_PIN M1 [get_ports {PMOD5}]
set_property PACKAGE_PIN L1 [get_ports {PMOD6}]

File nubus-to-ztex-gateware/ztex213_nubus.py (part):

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# I/O
_nubus_io_v1_0 = [
    ## leds on the NuBus board
    ("user_led", 0, Pins("V5"),  IOStandard("lvcmos33")), #LED0
    ("user_led", 1, Pins("V4"),  IOStandard("lvcmos33")), #LED1
    ## serial header for console
    ("serial", 0,
     Subsignal("tx", Pins("V9")), # FIXME: might be the other way round
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    ## extra 54 MHz clock reference for bank 34
    ("clk54", 0, Pins("R3"), IOStandard("LVCMOS33")),
    ## leds on the NuBus board
    ("user_led", 0, Pins("V9"),  IOStandard("lvcmos33")), #LED0
    ("user_led", 1, Pins("U9"),  IOStandard("lvcmos33")), #LED1; both are overlapping with serial TX/RX
    ## serial header for console
    ("serial", 0,
     Subsignal("tx", Pins("V9")), # FIXME: might be the other way round
     Subsignal("rx", Pins("U9")), # both are overlapping with LED0/1
     IOStandard("LVCMOS33")
    ),
    ## USB
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    ("tm1_3v3_n",          0, Pins("J17"), IOStandard("lvttl")),
    ("tm2_3v3_n",          0, Pins("T4"),  IOStandard("lvttl")),
    
    ("nubus_oe",           0, Pins("G13"), IOStandard("lvttl")),
    ("nubus_ad_dir",       0, Pins("G16"), IOStandard("lvttl")),
    ("nubus_master_dir",   0, Pins("H17"), IOStandard("lvttl")),
    ("grant",              0, Pins("H15"), IOStandard("lvttl")),
    ("arbcy_n",            0, Pins("J13"), IOStandard("lvttl")), # arb in the schematics
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    ("clk_3v3_n",          0, Pins("H16"), IOStandard("lvttl")),
    ("clk2x_3v3_n",        0, Pins("T5"),  IOStandard("lvttl")),
    ("ack_3v3_n",          0, Pins("J17"), IOStandard("lvttl")),
    ("ack_o_n",            0, Pins("H14"), IOStandard("lvttl")),
    ("ack_oe_n",           0, Pins("J13"), IOStandard("lvttl")),
    ("nmrq_3v3_n",         0, Pins("K16"), IOStandard("lvttl")), # 'irq' line, Output only direct to 74LVT125
    ("reset_3v3_n",        0, Pins("U8"),  IOStandard("lvttl")), # Input only
    ("rqst_3v3_n"  ,       0, Pins("J18"), IOStandard("lvttl")), # Open Collector
    ("rqst_o_n"  ,         0, Pins("K13"), IOStandard("lvttl")),
    ("start_3v3_n",        0, Pins("K15"), IOStandard("lvttl")),
    ("start_o_n",          0, Pins("H15"), IOStandard("lvttl")),
    ("start_oe_n",         0, Pins("J15"), IOStandard("lvttl")),
    ("ad_3v3_n",           0, Pins("A13 A14 C12 B12 B13 B14 A15 A16 "
                                   "D12 D13 D14 C14 B16 B17 D15 C15 "
                                   "B18 A18 C16 C17 E15 E16 F14 F13 "
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    ("tm0_o_n",            0, Pins("T6"), IOStandard("lvttl")),
    ("tm1_3v3_n",          0, Pins("V2"), IOStandard("lvttl")),
    ("tm1_o_n",            0, Pins("R7"), IOStandard("lvttl")),
    ("tmx_oe_n",           0, Pins("R8"), IOStandard("lvttl")),
    ("tm2_3v3_n",          0, Pins("K6"),  IOStandard("lvttl")),
    ("tm2_o_n",            0, Pins("R5"),  IOStandard("lvttl")),
    ("tm2_oe_n",           0, Pins("R6"),  IOStandard("lvttl")),
    
    ("nubus_oe",           0, Pins("G13"), IOStandard("lvttl")),
    ("nubus_ad_dir",       0, Pins("G17"), IOStandard("lvttl")),
]

# Connectors ---------------------------------------------------------------------------------------
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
